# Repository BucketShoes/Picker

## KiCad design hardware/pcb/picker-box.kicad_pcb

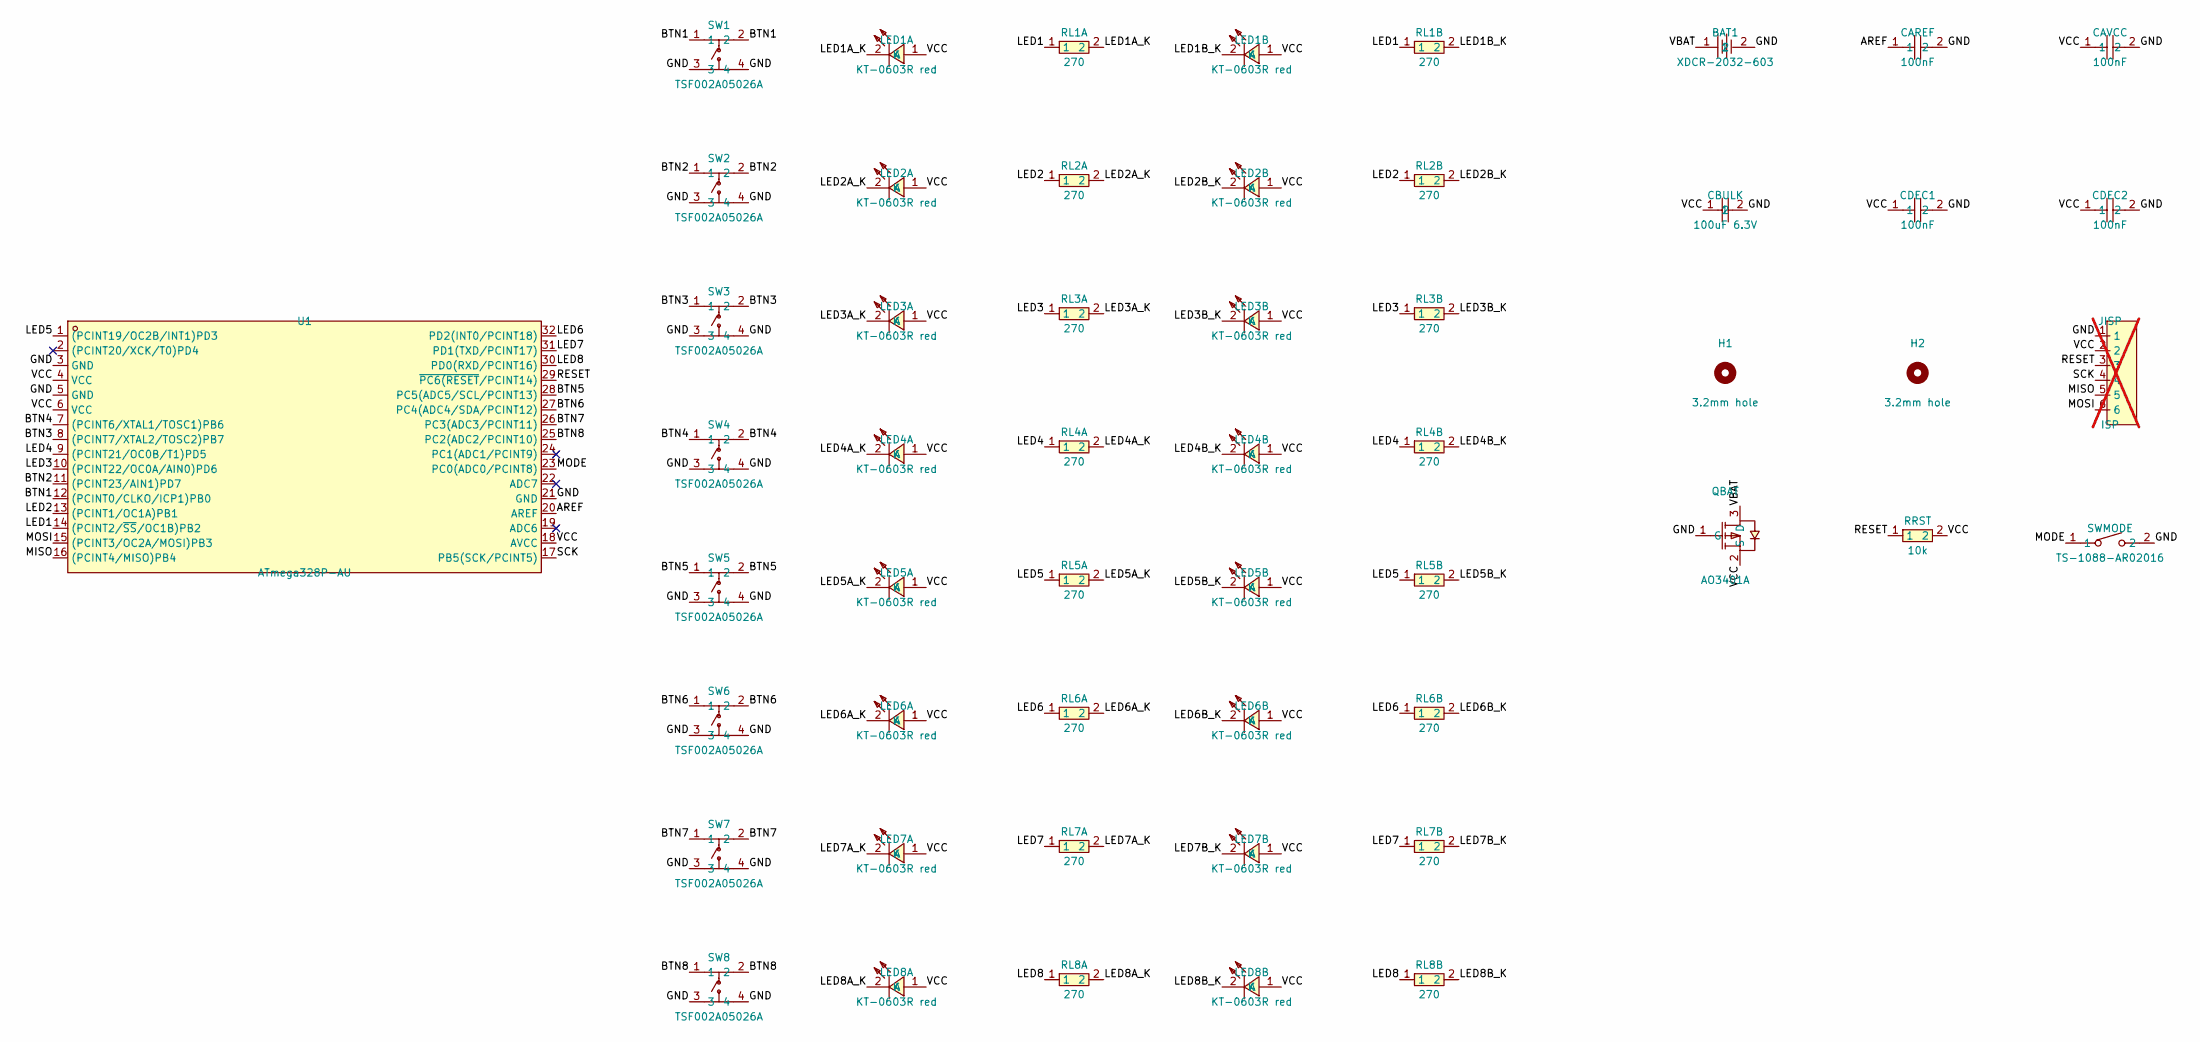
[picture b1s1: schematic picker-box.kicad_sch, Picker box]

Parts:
BAT1: XDCR-2032-603; BAT-SMD_XDCR-2032-603; LCSC Part # C7498148
CAREF: 100nF; C0603; LCSC Part # C14663
CAVCC: 100nF; C0603; LCSC Part # C14663
CBULK: 100uF 6.3V; C1206; LCSC Part # C15008
CDEC1, CDEC2: 100nF; C0603; LCSC Part # C14663
H1, H2: 3.2mm hole; MountingHole_3.2mm_M3
JISP: ISP; HDR-TH_6P-P2.54-V-M-1; LCSC Part # C37208; not fitted
LED1A, LED1B, LED2A, LED2B, LED3A, LED3B, LED4A, LED4B, LED5A, LED5B, LED6A, LED6B, LED7A, LED7B, LED8A, LED8B: KT-0603R red; LED-SMD_L1.6-W0.8-R-RD; LCSC Part # C2286
QBAT: AO3401A; SOT-23_L2.9-W1.3-P1.90-LS2.4-BR; LCSC Part # C15127
RL1A, RL1B, RL2A, RL2B, RL3A, RL3B, RL4A, RL4B, RL5A, RL5B, RL6A, RL6B, RL7A, RL7B, RL8A, RL8B: 270; R0603; LCSC Part # C22966
RRST: 10k; R0603; LCSC Part # C25804
SW1, SW2, SW3, SW4, SW5, SW6, SW7, SW8: TSF002A05026A; KEY-SMD_4P-L12.0-W12.0-P5.00-LS15.0; LCSC Part # C2888710
SWMODE: TS-1088-AR02016; SW-SMD_L3.9-W3.0-P4.45; LCSC Part # C720477
U1: ATmega328P-AU; TQFP-32_L7.0-W7.0-P0.80-LS9.0-BL; LCSC Part # C14877

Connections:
/AREF: CAREF.1, U1.20 (AREF)
/BTN1: SW1.1, SW1.2, U1.12 ((PCINT0/CLKO/ICP1)PB0)
/BTN2: SW2.1, SW2.2, U1.11 ((PCINT23/AIN1)PD7)
/BTN3: SW3.1, SW3.2, U1.8 ((PCINT7/XTAL2/TOSC2)PB7)
/BTN4: SW4.1, SW4.2, U1.7 ((PCINT6/XTAL1/TOSC1)PB6)
/BTN5: SW5.1, SW5.2, U1.28 (PC5(ADC5/SCL/PCINT13))
/BTN6: SW6.1, SW6.2, U1.27 (PC4(ADC4/SDA/PCINT12))
/BTN7: SW7.1, SW7.2, U1.26 (PC3(ADC3/PCINT11))
/BTN8: SW8.1, SW8.2, U1.25 (PC2(ADC2/PCINT10))
/GND: BAT1.2, CAREF.2, CAVCC.2, CBULK.2, CDEC1.2, CDEC2.2, JISP.1, QBAT.1 (G), SW1.3, SW1.4, SW2.3, SW2.4, SW3.3, SW3.4, SW4.3, SW4.4, SW5.3, SW5.4, SW6.3, SW6.4, SW7.3, SW7.4, SW8.3, SW8.4, SWMODE.2, U1.3 (GND), U1.5 (GND), U1.21 (GND)
/LED1: RL1A.1, RL1B.1, U1.14 ((PCINT2/~SS/OC1B)PB2)
/LED1A_K: LED1A.2 (K), RL1A.2
/LED1B_K: LED1B.2 (K), RL1B.2
/LED2: RL2A.1, RL2B.1, U1.13 ((PCINT1/OC1A)PB1)
/LED2A_K: LED2A.2 (K), RL2A.2
/LED2B_K: LED2B.2 (K), RL2B.2
/LED3: RL3A.1, RL3B.1, U1.10 ((PCINT22/OC0A/AIN0)PD6)
/LED3A_K: LED3A.2 (K), RL3A.2
/LED3B_K: LED3B.2 (K), RL3B.2
/LED4: RL4A.1, RL4B.1, U1.9 ((PCINT21/OC0B/T1)PD5)
/LED4A_K: LED4A.2 (K), RL4A.2
/LED4B_K: LED4B.2 (K), RL4B.2
/LED5: RL5A.1, RL5B.1, U1.1 ((PCINT19/OC2B/INT1)PD3)
/LED5A_K: LED5A.2 (K), RL5A.2
/LED5B_K: LED5B.2 (K), RL5B.2
/LED6: RL6A.1, RL6B.1, U1.32 (PD2(INT0/PCINT18))
/LED6A_K: LED6A.2 (K), RL6A.2
/LED6B_K: LED6B.2 (K), RL6B.2
/LED7: RL7A.1, RL7B.1, U1.31 (PD1(TXD/PCINT17))
/LED7A_K: LED7A.2 (K), RL7A.2
/LED7B_K: LED7B.2 (K), RL7B.2
/LED8: RL8A.1, RL8B.1, U1.30 (PD0(RXD/PCINT16))
/LED8A_K: LED8A.2 (K), RL8A.2
/LED8B_K: LED8B.2 (K), RL8B.2
/MISO: JISP.5, U1.16 ((PCINT4/MISO)PB4)
/MODE: SWMODE.1, U1.23 (PC0(ADC0/PCINT8))
/MOSI: JISP.6, U1.15 ((PCINT3/OC2A/MOSI)PB3)
/RESET: JISP.3, RRST.1, U1.29 (~PC6(RESET/PCINT14))
/SCK: JISP.4, U1.17 (PB5(SCK/PCINT5))
/VBAT: BAT1.1, QBAT.3 (D)
/VCC: CAVCC.1, CBULK.1, CDEC1.1, CDEC2.1, JISP.2, LED1A.1 (A), LED1B.1 (A), LED2A.1 (A), LED2B.1 (A), LED3A.1 (A), LED3B.1 (A), LED4A.1 (A), LED4B.1 (A), LED5A.1 (A), LED5B.1 (A), LED6A.1 (A), LED6B.1 (A), LED7A.1 (A), LED7B.1 (A), LED8A.1 (A), LED8B.1 (A), QBAT.2 (S), RRST.2, U1.4 (VCC), U1.6 (VCC), U1.18 (AVCC)

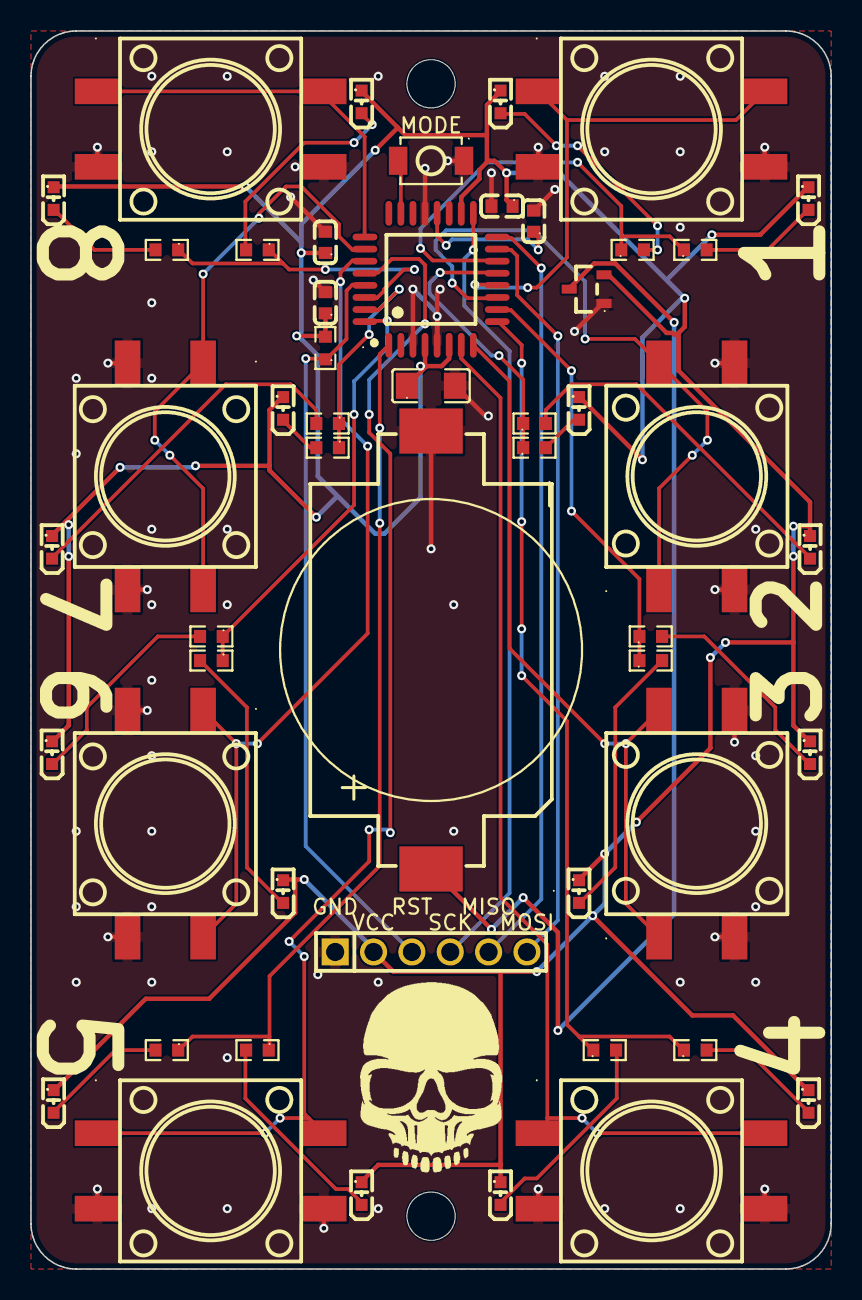
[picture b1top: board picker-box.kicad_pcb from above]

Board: 2 copper layers, 53.0 x 82.0 mm, 53 parts (0 on the bottom side), 41 nets.

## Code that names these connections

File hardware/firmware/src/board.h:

// Pin map, as on the board (hardware/design.md, "Pin map"). Seat n is index n-1, clockwise from the top right.
// Routing may still swap pins within a category: only these tables change.
#pragma once
#include <avr/io.h>
#include <stdint.h>

#define SEATS 8
#define MODE_BIT (1u << 8)    // bit 8 of a button mask; bits 0-7 are the seats
#define SEAT_BITS 0xFFu

// LEDs sink: anode to VCC, cathode through 270 R to the pin, so a low pin lights both LEDs of that seat.
// One entry per seat: its bit on PORTB or PORTD (0 = not on that port).
static const uint8_t LED_B[SEATS] = {_BV(PB2), _BV(PB1), 0, 0, 0, 0, 0, 0};
static const uint8_t LED_D[SEATS] = {0, 0, _BV(PD6), _BV(PD5), _BV(PD3), _BV(PD2), _BV(PD1), _BV(PD0)};
#define LED_PB (_BV(PB2) | _BV(PB1))
#define LED_PD (_BV(PD6) | _BV(PD5) | _BV(PD3) | _BV(PD2) | _BV(PD1) | _BV(PD0))

// Buttons to GND with the internal pull-up. Index 8 is MODE.
static const uint8_t BTN_B[SEATS + 1] = {_BV(PB0), 0, _BV(PB7), _BV(PB6), 0, 0, 0, 0, 0};
static const uint8_t BTN_C[SEATS + 1] = {0, 0, 0, 0, _BV(PC5), _BV(PC4), _BV(PC3), _BV(PC2), _BV(PC0)};
static const uint8_t BTN_D[SEATS + 1] = {0, _BV(PD7), 0, 0, 0, 0, 0, 0, 0};
#define BTN_PB (_BV(PB0) | _BV(PB7) | _BV(PB6))
#define BTN_PC (_BV(PC5) | _BV(PC4) | _BV(PC3) | _BV(PC2) | _BV(PC0))
#define BTN_PD (_BV(PD7))

// Every other I/O pin is an input with its pull-up on, so nothing floats in sleep:
// PB3-PB5 (ISP), PD4 and PC1 (spare). PC6 is RESET. On the 328PB, PE2/PE3 (spare) too, but never PE0/PE1:
// they are tied to GND and VCC so either chip fits, and a pull-up on PE0 would leak into GND.
#define PULL_PB (BTN_PB | _BV(PB3) | _BV(PB4) | _BV(PB5))
#define PULL_PC (BTN_PC | _BV(PC1))
#define PULL_PD (BTN_PD | _BV(PD4))

// Port values with every LED off: what the PWM writes, with lit LEDs' bits cleared.
#define IDLE_PB (PULL_PB | LED_PB)
#define IDLE_PD (PULL_PD | LED_PD)

void board_init();
uint16_t btn_raw();   // pressed buttons right now (no debounce)
void btn_port_masks(uint16_t m, uint8_t *b, uint8_t *c, uint8_t *d);
